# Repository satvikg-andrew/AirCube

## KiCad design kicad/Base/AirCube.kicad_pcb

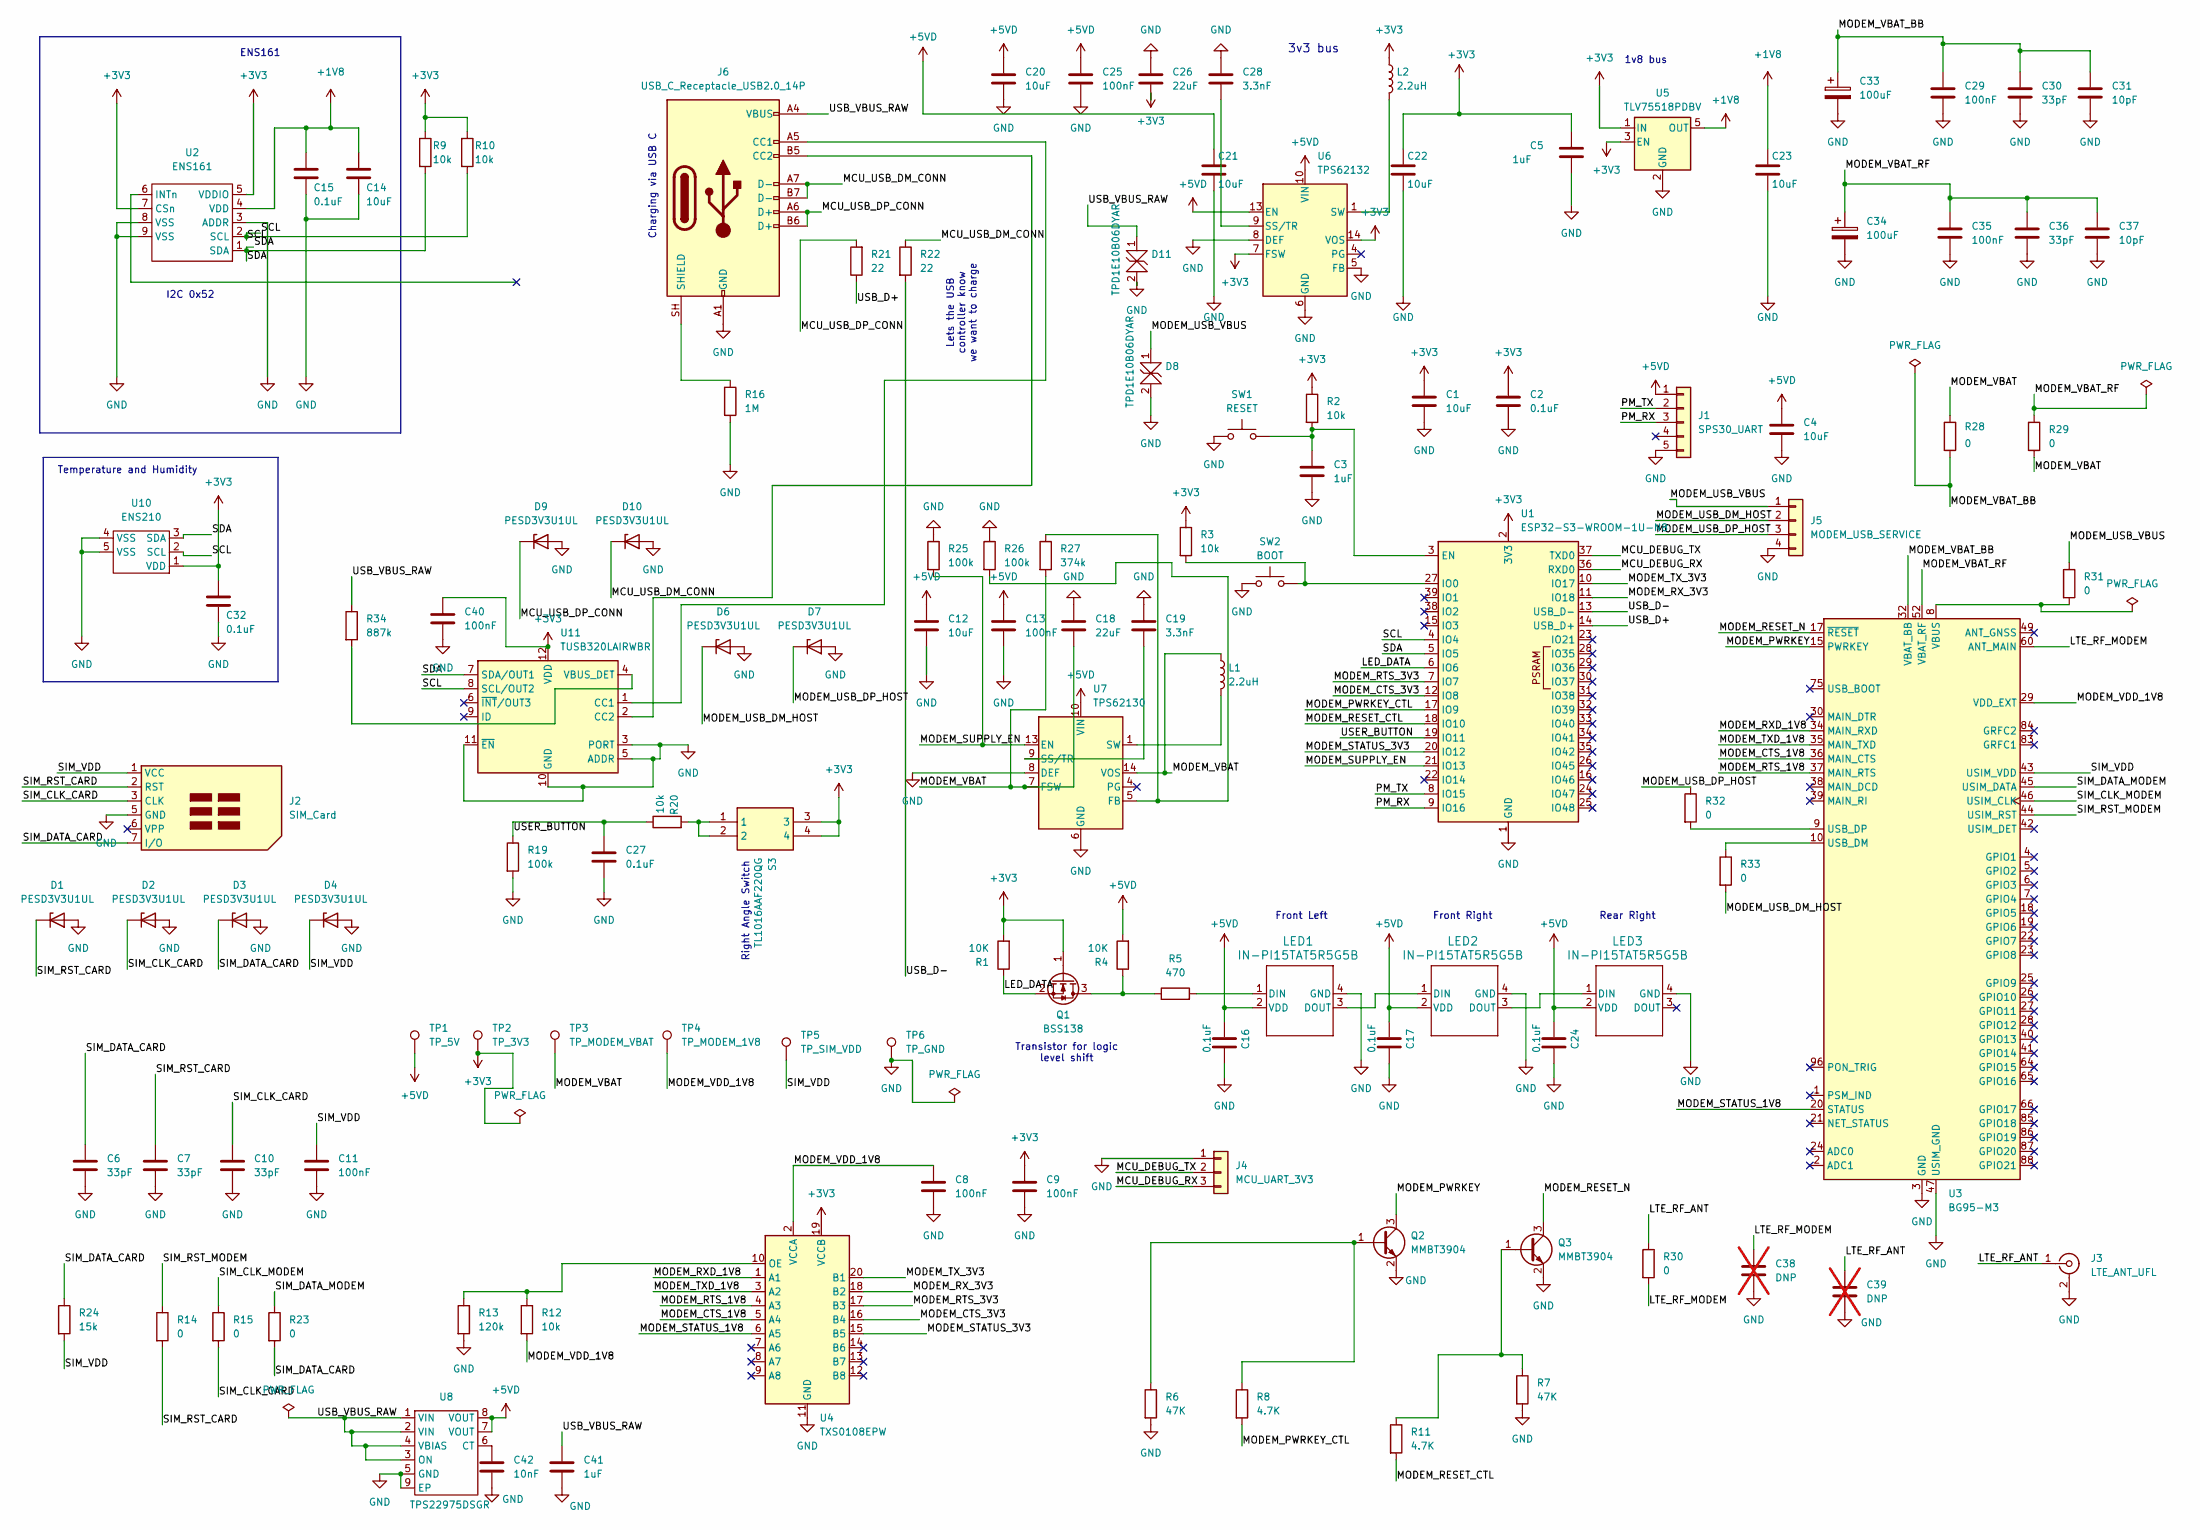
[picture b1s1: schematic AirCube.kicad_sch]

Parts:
C1, C4, C12, C20: 10uF; C_0805_2012Metric
C2, C15, C16, C17, C24, C27, C32: 0.1uF; C_0603_1608Metric
C3, C5, C41: 1uF; C_0603_1608Metric
C6, C7, C10, C30, C36: 33pF; C_0603_1608Metric
C8, C9, C11, C13, C25, C29, C35, C40: 100nF; C_0603_1608Metric
C14, C21, C22, C23: 10uF; C_0603_1608Metric
C18, C26: 22uF; C_1210_3225Metric
C19, C28: 3.3nF; C_0603_1608Metric
C31, C37: 10pF; C_0603_1608Metric
C33, C34: 100uF; CP_EIA-3528-21_Kemet-B
C38, C39: DNP; C_0402_1005Metric; not fitted
C42: 10nF; C_0603_1608Metric
D1, D2, D3, D4, D6, D7, D9, D10: PESD3V3U1UL; D_SOD-882
D8, D11: TPD1E10B06DYAR; D_SOD-523
J1: SPS30_UART; JST_ZH_B5B-ZR_1x05_P1.50mm_Vertical
J2: SIM_Card; nanoSIM_GCT_SIM8060-6-0-14-00_GroundedShell
J3: LTE_ANT_UFL; U.FL_Hirose_U.FL-R-SMT-1_Vertical
J4: MCU_UART_3V3; PinHeader_1x03_P2.54mm_Vertical
J5: MODEM_USB_SERVICE; PinHeader_1x04_P2.54mm_Vertical
J6: USB_C_Receptacle_USB2.0_14P; USB_C_Receptacle_GCT_USB4105-xx-A_16P_TopMnt_Horizontal
L1, L2: 2.2uH; L_Coilcraft_XAL4020-XXX
LED1, LED2, LED3: IN-PI15TAT5R5G5B; IN-PI15_INL
Q1: BSS138; SOT-23
Q2, Q3: MMBT3904; SOT-23
R1, R4: 10K; R_0603_1608Metric
R2, R3, R9, R10, R12, R20: 10k; R_0603_1608Metric
R5: 470; R_0603_1608Metric
R6, R7: 47K; R_0603_1608Metric
R8, R11: 4.7K; R_0603_1608Metric
R13: 120k; R_0603_1608Metric
R14, R15, R23, R31, R32, R33: 0; R_0603_1608Metric
R16: 1M; R_0603_1608Metric
R19, R25, R26: 100k; R_0603_1608Metric
R21, R22: 22; R_0603_1608Metric
R24: 15k; R_0603_1608Metric
R27: 374k; R_0603_1608Metric
R28, R29: 0; R_0805_2012Metric
R30: 0; R_0402_1005Metric
R34: 887k; R_0603_1608Metric
S3: TL1016AAF220QG; Mouser Part Number 612-TL1016AAF220QG
SW1: RESET; SW_SPST_TL3305A
SW2: BOOT; SW_SPST_TL3305A
TP1: TP_5V; TestPoint_Pad_D1.5mm
TP2: TP_3V3; TestPoint_Pad_D1.5mm
TP3: TP_MODEM_VBAT; TestPoint_Pad_D1.5mm
TP4: TP_MODEM_1V8; TestPoint_Pad_D1.5mm
TP5: TP_SIM_VDD; TestPoint_Pad_D1.5mm
TP6: TP_GND; TestPoint_Pad_D1.5mm
U1: ESP32-S3-WROOM-1U-N8; ESP32-S3-WROOM-1U_ThermalDrill0.30
U2: ENS161
U3: BG95-M3; Quectel_BG95
U4: TXS0108EPW; TSSOP-20_4.4x6.5mm_P0.65mm
U5: TLV75518PDBV; SOT-23-5
U6: TPS62132; TPS6213x_RGT_ThermalDrill0.30
U7: TPS62130; TPS6213x_RGT_ThermalDrill0.30
U8: TPS22975DSGR; TPS22975_DSG_TI_LandPattern
U10: ENS210
U11: TUSB320LAIRWBR; Texas_X2QFN-12_1.6x1.6mm_P0.4mm

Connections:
+1V8: C14.1, C15.1, C23.1, U2.4 (VDD), U5.5 (OUT)
+3V3: C1.1, C2.1, C5.1, C9.1, C22.1, C26.2, C32.1, C40.1, L2.1, Q1.1 (G), R1.2, R2.1, R3.1, R9.1, R10.1, S3.3, S3.4, TP2.1 (1_1), U1.2 (3V3), U2.5 (VDDIO), U2.7 (CSn), U4.19 (VCCB), U5.1 (IN), U5.3 (EN), U6.7 (FSW), U6.14 (VOS), U10.1 (VDD), U11.12 (VDD)
+5VD: C4.1, C12.1, C13.1, C16.1, C17.1, C20.1, C21.1, C24.1, C25.1, J1.1, LED1.2 (VDD), LED2.2 (VDD), LED3.2 (VDD), R4.2, TP1.1 (1_1), U6.10 (VIN), U6.11 (VIN), U6.12 (VIN), U6.13 (EN), U7.10 (VIN), U7.11 (VIN), U7.12 (VIN), U8.7 (VOUT), U8.8 (VOUT)
/LED_DATA: Q1.2 (S), R1.1, U1.6 (IO6)
/LTE_RF_ANT: C39.1, J3.1 (In), R30.1
/LTE_RF_MODEM: C38.1, R30.2, U3.60 (ANT_MAIN)
/MCU_DEBUG_RX: J4.3, U1.36 (RXD0)
/MCU_DEBUG_TX: J4.2, U1.37 (TXD0)
/MCU_USB_DM_CONN: D10.1 (K), J6.A7 (D-), J6.B7 (D-), R22.1
/MCU_USB_DP_CONN: D9.1 (K), J6.A6 (D+), J6.B6 (D+), R21.2
/MODEM_CTS_1V8: U3.36 (MAIN_CTS), U4.5 (A4)
/MODEM_CTS_3V3: U1.12 (IO8), U4.16 (B4)
/MODEM_PWRKEY: Q2.3 (C), U3.15 (PWRKEY)
/MODEM_PWRKEY_CTL: R8.2, U1.17 (IO9)
/MODEM_RESET_CTL: R11.2, U1.18 (IO10)
/MODEM_RESET_N: Q3.3 (C), U3.17 (~RESET)
/MODEM_RTS_1V8: U3.37 (MAIN_RTS), U4.4 (A3)
/MODEM_RTS_3V3: U1.7 (IO7), U4.17 (B3)
/MODEM_RXD_1V8: U3.34 (MAIN_RXD), U4.1 (A1)
/MODEM_RX_3V3: U1.11 (IO18), U4.18 (B2)
/MODEM_STATUS_1V8: U3.20 (STATUS), U4.6 (A5)
/MODEM_STATUS_3V3: U1.20 (IO12), U4.15 (B5)
/MODEM_SUPPLY_EN: R25.2, U1.21 (IO13), U7.13 (EN)
/MODEM_TXD_1V8: U3.35 (MAIN_TXD), U4.3 (A2)
/MODEM_TX_3V3: U1.10 (IO17), U4.20 (B1)
/MODEM_USB_DM_HOST: D6.1 (K), J5.2, R33.2
/MODEM_USB_DP_HOST: D7.1 (K), J5.3, R32.1
/MODEM_USB_VBUS: D8.1, J5.1, R31.1
/MODEM_VBAT: C18.2, L1.1, R27.2, R28.1, R29.2, TP3.1 (1_1), U7.7 (FSW), U7.14 (VOS)
/MODEM_VBAT_BB: C29.1, C30.1, C31.1, C33.1, R28.2, U3.32 (VBAT_BB), U3.33 (VBAT_BB)
/MODEM_VBAT_RF: C34.1, C35.1, C36.1, C37.1, R29.1, U3.52 (VBAT_RF), U3.53 (VBAT_RF)
/MODEM_VDD_1V8: C8.1, R12.2, TP4.1 (1_1), U3.29 (VDD_EXT), U4.2 (VCCA)
/PM_RX: J1.3, U1.9 (IO16)
/PM_TX: J1.2, U1.8 (IO15)
/SCL: R10.2, U1.4 (IO4), U2.2 (SCL), U10.2 (SCL), U11.8 (SCL/OUT2)
/SDA: R9.2, U1.5 (IO5), U2.1 (SDA), U10.3 (SDA), U11.7 (SDA/OUT1)
/SIM_CLK_CARD: C10.1, D2.1 (K), J2.3 (CLK), R15.2
/SIM_CLK_MODEM: R15.1, U3.46 (USIM_CLK)
/SIM_DATA_CARD: C6.1, D3.1 (K), J2.7 (I/O), R23.2, R24.1
/SIM_DATA_MODEM: R23.1, U3.45 (USIM_DATA)
/SIM_RST_CARD: C7.1, D1.1 (K), J2.2 (RST), R14.2
/SIM_RST_MODEM: R14.1, U3.44 (USIM_RST)
/SIM_VDD: C11.1, D4.1 (K), J2.1 (VCC), R24.2, TP5.1 (1_1), U3.43 (USIM_VDD)
/USB_D+: R21.1, U1.14 (USB_D+)
/USB_D-: R22.2, U1.13 (USB_D-)
/USB_VBUS_RAW: C41.1, D11.1, J6.A4 (VBUS), J6.A9 (VBUS), J6.B4 (VBUS), J6.B9 (VBUS), R34.1, U8.1 (VIN), U8.2 (VIN), U8.3 (ON), U8.4 (VBIAS)
/USER_BUTTON: C27.1, R19.1, R20.1, U1.19 (IO11)
GND: C1.2, C2.2, C3.2, C4.2, C5.2, C6.2, C7.2, C8.2, C9.2, C10.2, C11.2, C12.2, C13.2, C14.2, C15.2, C16.2, C17.2, C18.1, C19.1, C20.2, C21.2, C22.2, C23.2, C24.2, C25.2, C26.1, C27.2, C28.1, C29.2, C30.2, C31.2, C32.2, C33.2, C34.2, C35.2, C36.2, C37.2, C38.2, C39.2, C40.2, C41.2, C42.2, D1.2 (A), D2.2 (A), D3.2 (A), D4.2 (A), D6.2 (A), D7.2 (A), D8.2, D9.2 (A), D10.2 (A), D11.2, J1.5, J2.5 (GND), J3.2 (Ext), J4.1, J5.4, J6.A1 (GND), J6.A12 (GND), J6.B1 (GND), J6.B12 (GND), LED1.4 (GND), LED2.4 (GND), LED3.4 (GND), Q2.2 (E), Q3.2 (E), R6.2, R7.2, R13.2, R16.2, R19.2, R25.1, R26.1, SW1.1, SW2.1, TP6.1 (1_1), U1.1 (GND), U1.40 (GND), U1.41 (GND), U2.3 (ADDR), U2.8 (VSS), U2.9 (VSS), U3.3 (GND), U3.31 (GND), U3.47 (USIM_GND), U3.48 (GND), U3.50 (GND), U3.54 (GND), U3.55 (GND), U3.58 (GND), U3.59 (GND), U3.61 (GND), U3.62 (GND), U3.67 (GND), U3.68 (GND), U3.69 (GND), U3.70 (GND), U3.71 (GND), U3.72 (GND), U3.73 (GND), U3.74 (GND), U3.79 (GND), U3.80 (GND), U3.81 (GND), U3.82 (GND), U3.89 (GND), U3.90 (GND), U3.91 (GND), U3.100 (GND), U3.101 (GND), U3.102 (GND), U4.11 (GND), U5.2 (GND), U6.5 (FB), U6.6 (GND), U6.8 (DEF), U6.15 (GND), U6.16 (GND), U6.17 (GND), U7.6 (GND), U7.8 (DEF), U7.15 (GND), U7.16 (GND), U7.17 (GND), U8.5 (GND), U8.9 (EP), U10.4 (VSS), U10.5 (VSS), U11.3 (PORT), U11.5 (ADDR), U11.10 (GND), U11.11 (~EN)
unnamed: J6.A5 (CC1), U11.1 (CC1)
unnamed: J6.B5 (CC2), U11.2 (CC2)
unnamed: J6.SH (SHIELD), R16.1
unnamed: L1.2, U7.1 (SW), U7.2 (SW), U7.3 (SW)
unnamed: L2.2, U6.1 (SW), U6.2 (SW), U6.3 (SW)
unnamed: LED1.1 (DIN), R5.2
unnamed: LED1.3 (DOUT), LED2.1 (DIN)
unnamed: LED2.3 (DOUT), LED3.1 (DIN)
unnamed: Q1.3 (D), R4.1, R5.1
unnamed: Q2.1 (B), R6.1, R8.1
unnamed: Q3.1 (B), R7.1, R11.1
unnamed: R20.2, S3.1, S3.2
unnamed: C3.1, R2.2, SW1.2, U1.3 (EN)
unnamed: R3.2, SW2.2, U1.27 (IO0)
unnamed: R33.1, U3.10 (USB_DM)
unnamed: R32.2, U3.9 (USB_DP)
unnamed: R31.2, U3.8 (VBUS)
unnamed: R12.1, R13.1, U4.10 (OE)
unnamed: C28.2, U6.9 (SS/TR)
unnamed: R26.2, R27.1, U7.5 (FB)
unnamed: C19.2, U7.9 (SS/TR)
unnamed: C42.1, U8.6 (CT)
unnamed: R34.2, U11.4 (VBUS_DET)

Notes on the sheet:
Charging via USB C
Rear Right
Transistor for logic level shift
1v8 bus
Right Angle Switch
Lets the USB controller know we want to charge
Front Right
ENS161
3v3 bus
Front Left
I2C 0x52
Temperature and Humidity

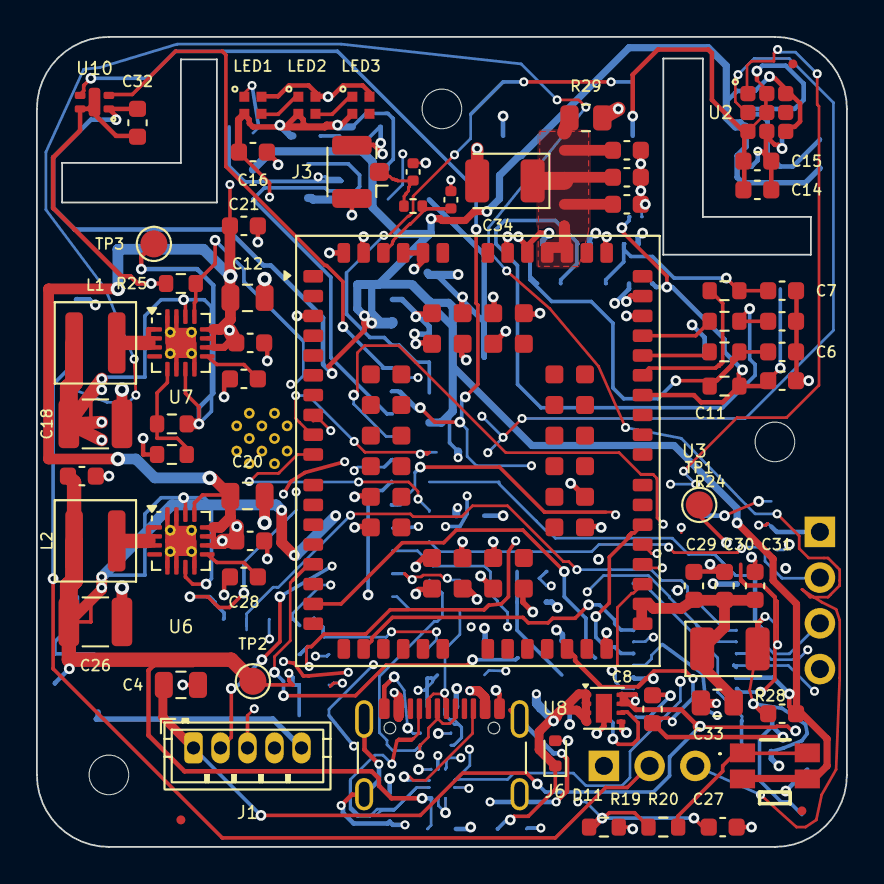
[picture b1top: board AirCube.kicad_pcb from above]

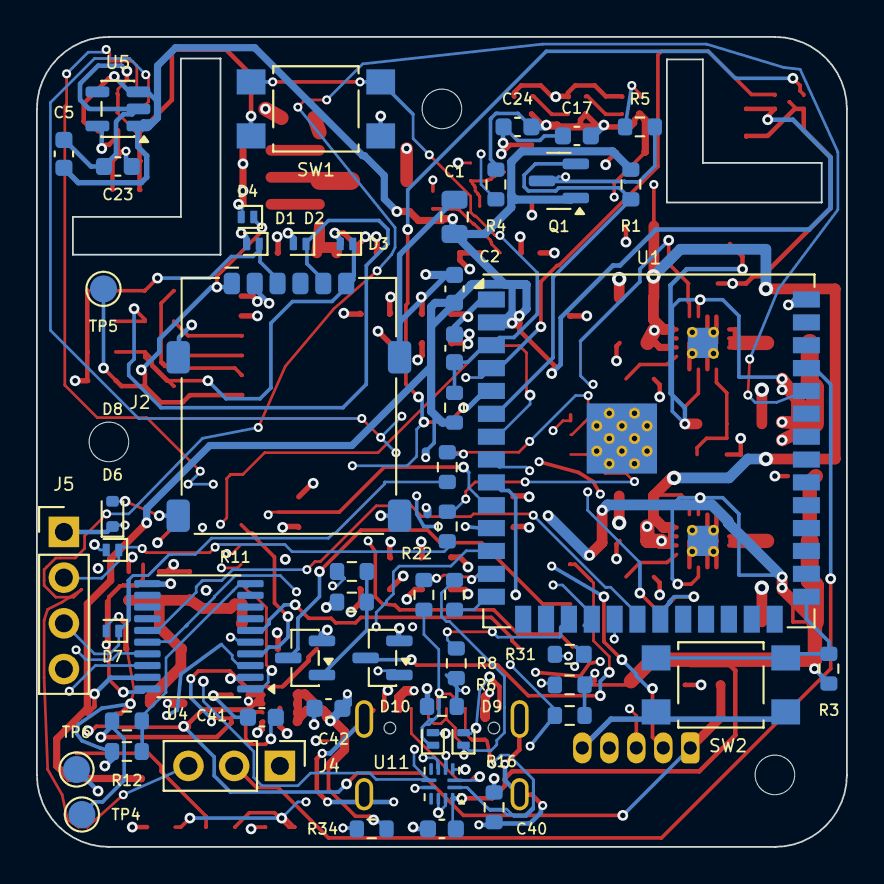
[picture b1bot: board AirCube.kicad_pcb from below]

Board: 4 copper layers, 45.0 x 45.0 mm, 117 parts (54 on the bottom side), 71 nets.
